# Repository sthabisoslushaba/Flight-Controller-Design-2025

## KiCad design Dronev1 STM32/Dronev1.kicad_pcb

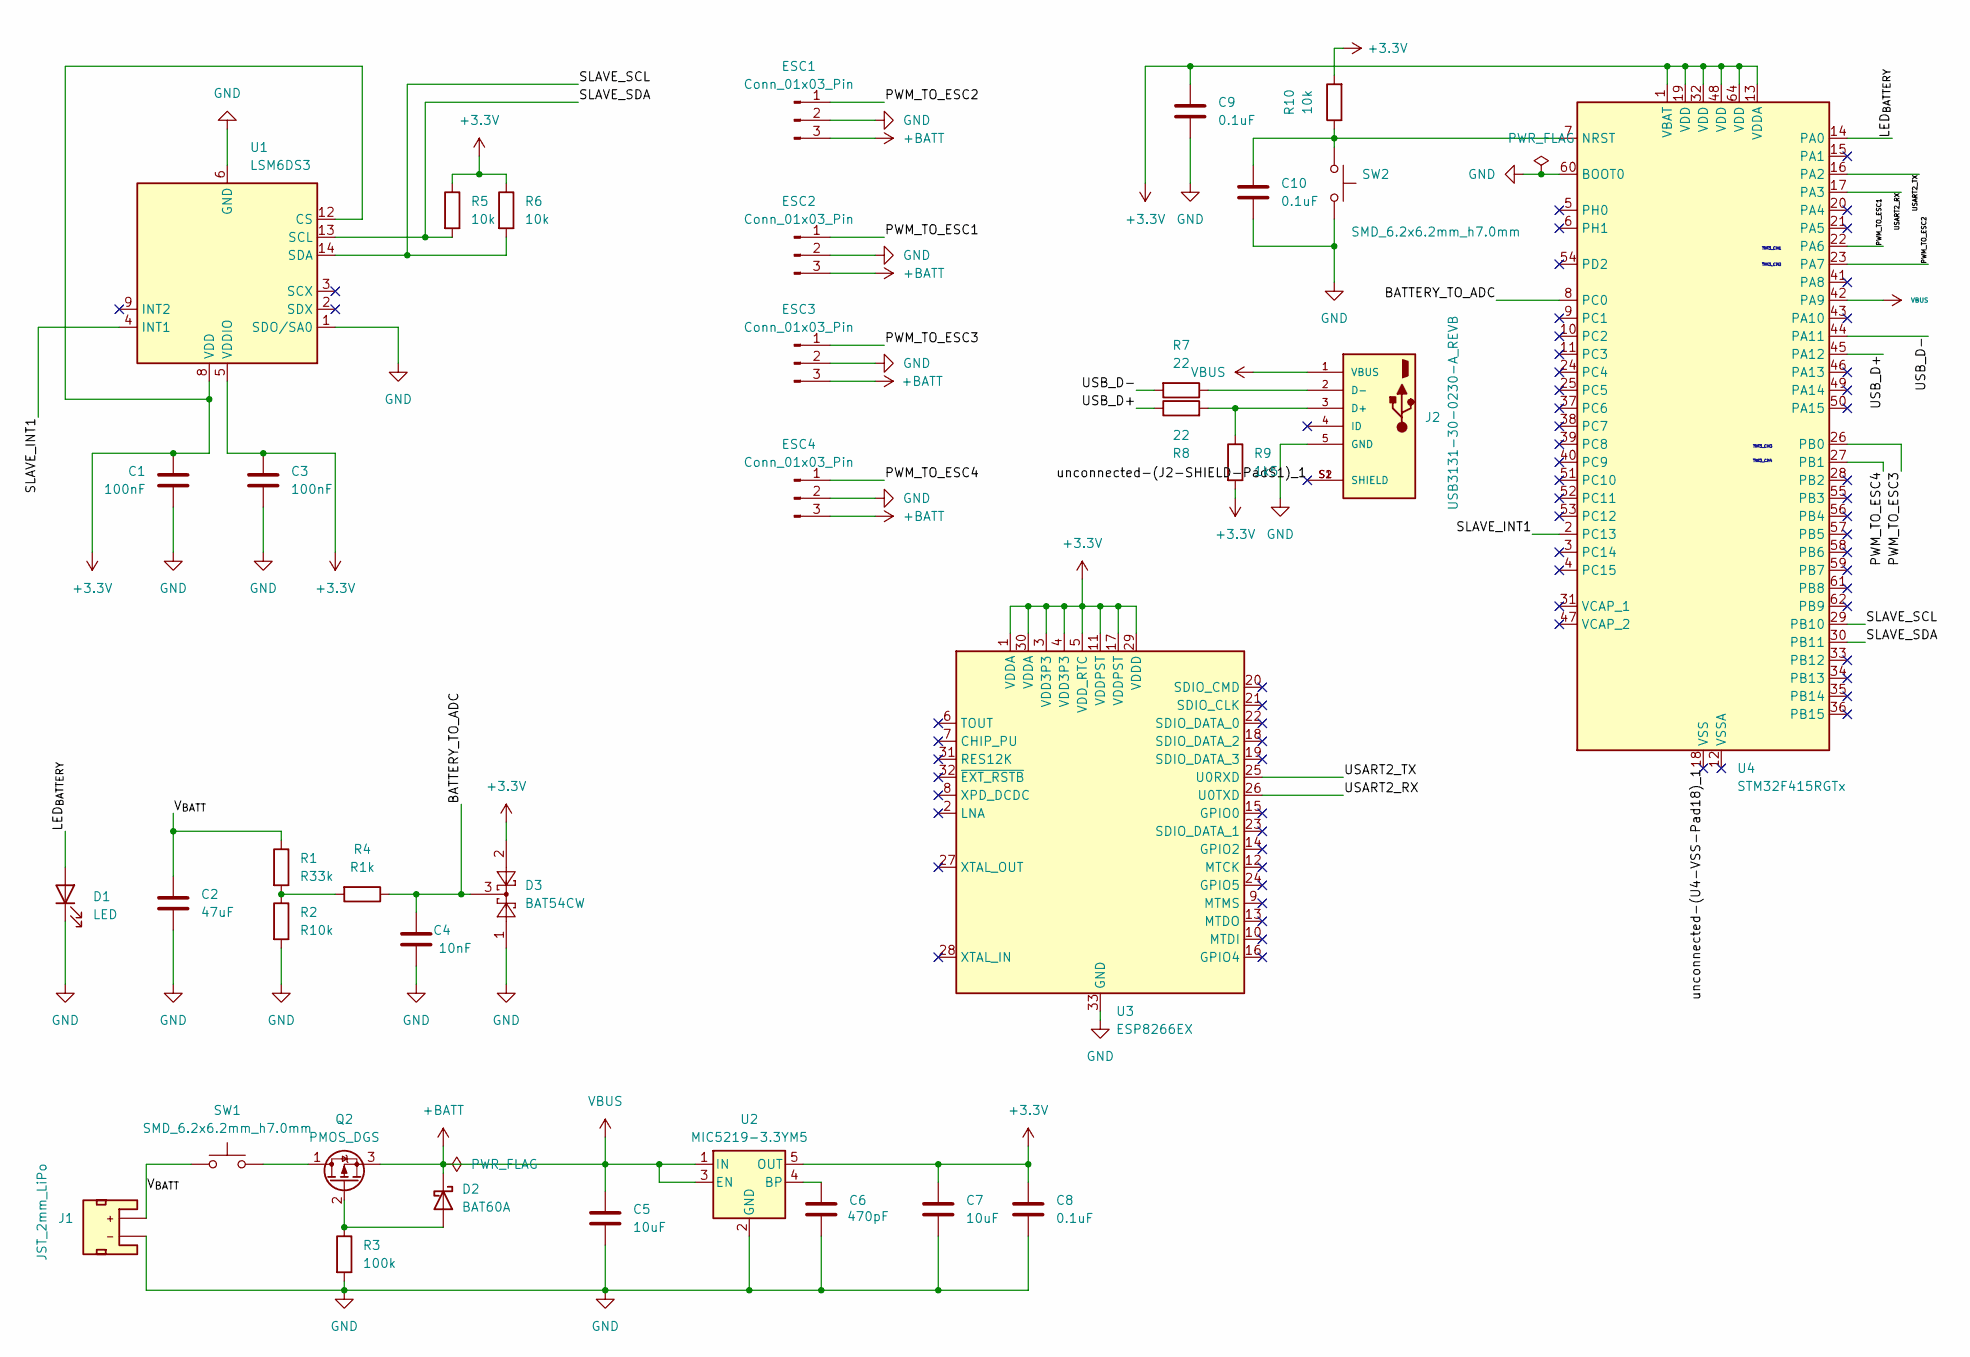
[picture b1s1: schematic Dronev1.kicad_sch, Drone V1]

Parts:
C1, C3: 100nF; CAPC1005X55N
C2: 47uF; CAPC2012X145N
C4: 10nF; CAPC1608X90N
C5, C7: 10uF; CAP_EEEFN1J100L
C6: 470pF; CAPC1608X90N
C8, C9, C10: 0.1uF; CAPC1005X55N
D1: LED; LED_1206_3216Metric_Red
D2: BAT60A; D_SOD-323
D3: BAT54CW; SOT-323_SC-70
ESC1, ESC2, ESC3, ESC4: Conn_01x03_Pin; 1x03_P2.54mm
J1: JST_2mm_LiPo; JST_1x02_P2.0mm_Horizontal_SMD
J2: USB3131-30-0230-A_REVB; GCT_USB3131-30-0230-A_REVB; PARTREV B4
Q2: PMOS_DGS; SOT23-3
R1: R33k; RES_ERJS02F3302X
R2: R10k; RES_ERJS1TJ103U
R3: 100k; RESC0603X26N
R4: R1k; RES_ERJU06J102V
R5, R6, R10: 10k; RES_ERJS1TJ103U
R7, R8: 22; RES_ERJXGNJ220Y
R9: 1k5; RESC3216X70N
SW1, SW2: SMD_6.2x6.2mm_h7.0mm; Push_SMD_6.2x6.2mm; Mfg Part# 679-2384-2-ND
U1: LSM6DS3; LGA-14_3x2.5mm_P0.5mm_LayoutBorder3x4y
U2: MIC5219-3.3YM5; SOT-23-5
U3: ESP8266EX; QFN-32-1EP_5x5mm_P0.5mm_EP3.45x3.45mm
U4: STM32F415RGTx; LQFP-64_10x10mm_P0.5mm

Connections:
+3.3V: C1.1, C3.1, C7.1, C8.1, C9.1, D3.2, R5.1, R6.1, R9.2, R10.2, U1.5 (VDDIO), U1.8 (VDD), U1.12 (CS), U2.5 (OUT), U3.1 (VDDA), U3.3 (VDD3P3), U3.4 (VDD3P3), U3.5 (VDD_RTC), U3.11 (VDDPST), U3.17 (VDDPST), U3.29 (VDDD), U3.30 (VDDA), U4.1 (VBAT), U4.13 (VDDA), U4.19 (VDD), U4.32 (VDD), U4.48 (VDD), U4.64 (VDD)
+BATT: C5.1, D2.1 (K), ESC1.3, ESC2.3, ESC3.3, ESC4.3, J2.1 (VBUS), Q2.3 (S), U2.1 (IN), U2.3 (EN), U4.42 (PA9); also elsewhere on the board
/BATTERY_TO_ADC: C4.1, D3.3, R4.1, U4.8 (PC0)
/LED_{BATTERY}: D1.2 (A), U4.14 (PA0)
/PWM_TO_ESC1: ESC2.1, U4.22 (PA6)
/PWM_TO_ESC2: ESC1.1, U4.23 (PA7)
/PWM_TO_ESC3: ESC3.1, U4.26 (PB0)
/PWM_TO_ESC4: ESC4.1, U4.27 (PB1)
/SLAVE_INT1: U1.4 (INT1), U4.2 (PC13)
/SLAVE_SCL: R6.2, U1.14 (SDA), U4.29 (PB10)
/SLAVE_SDA: R5.2, U1.13 (SCL), U4.30 (PB11)
/USART2_RX: U3.26 (U0TXD), U4.17 (PA3)
/USART2_TX: U3.25 (U0RXD), U4.16 (PA2)
/USB_D+: R8.1, U4.45 (PA12)
/USB_D-: R7.2, U4.44 (PA11)
/V_{BATT}: C2.1, J1.2 (+), R1.1, SW1.1; also elsewhere on the board
GND: C1.2, C2.2, C3.2, C4.2, C5.2, C6.2, C7.2, C8.2, C9.2, C10.2, D1.1 (K), D3.1, ESC1.2, ESC2.2, ESC3.2, ESC4.2, J1.1 (-), J2.5 (GND), R2.2, R3.2, SW2.2, U1.1 (SDO/SA0), U1.6 (GND), U1.7 (GND), U2.2 (GND), U3.33 (GND), U4.60 (BOOT0); also elsewhere on the board
unnamed: D2.2 (A), Q2.2 (G), R3.1
unnamed 20: J2.3 (D+), R8.2, R9.1; also elsewhere on the board
unnamed 21: J2.2 (D-), R7.1; also elsewhere on the board
unnamed: J2.S1 (SHIELD), J2.S2 (SHIELD)
unnamed 23: Q2.1 (D), SW1.2; also elsewhere on the board
unnamed: R1.2, R2.1, R4.2
unnamed: C6.1, U2.4 (BP)
unnamed: C10.1, R10.1, SW2.1, U4.7 (NRST)

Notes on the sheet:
TIM3_CH3
TIM3_CH2
TIM3_CH1
TIM3_CH4

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
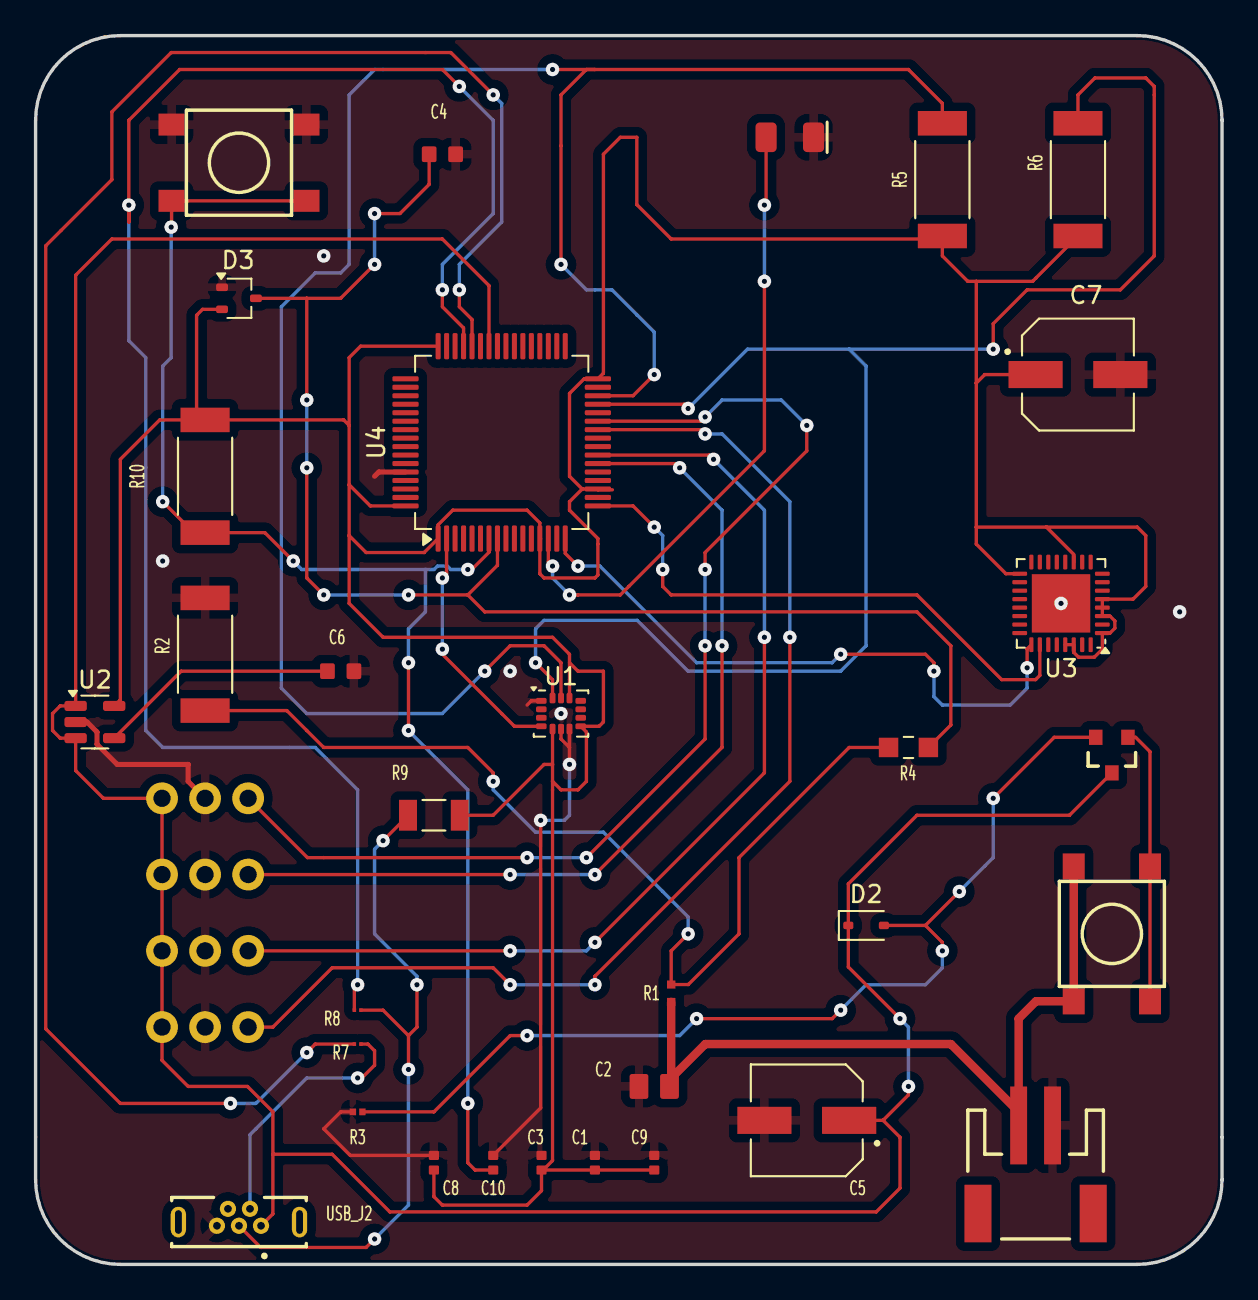
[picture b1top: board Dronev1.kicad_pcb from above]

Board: 2 copper layers, 70.0 x 72.5 mm, 36 parts (0 on the bottom side), 24 nets.

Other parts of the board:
ON/OFF: SMD_6.2x6.2mm_h7.0mm; Push_SMD_6.2x6.2mm
USB_J2: USB3131-30-0230-A_REVB; GCT_USB3131-30-0230-A_REVB

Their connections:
+BATT: USB_J2.1 (VBUS); also elsewhere on the board
/V_{BATT}: ON/OFF.1; also elsewhere on the board
GND: USB_J2.5 (GND); also elsewhere on the board
unnamed 20: USB_J2.3 (D+); also elsewhere on the board
unnamed 21: USB_J2.2 (D-); also elsewhere on the board
unnamed 23: ON/OFF.2; also elsewhere on the board

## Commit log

2025-10-01 Circuit complete, BOM generated, Footprints assigned, Moving to PCB Design
2025-10-02 Complete board with errors before optimization and fixes
2025-10-03 PCB complete, needs branding and attention to a few warnings but not critical
2025-10-05 friday the 3rd version
